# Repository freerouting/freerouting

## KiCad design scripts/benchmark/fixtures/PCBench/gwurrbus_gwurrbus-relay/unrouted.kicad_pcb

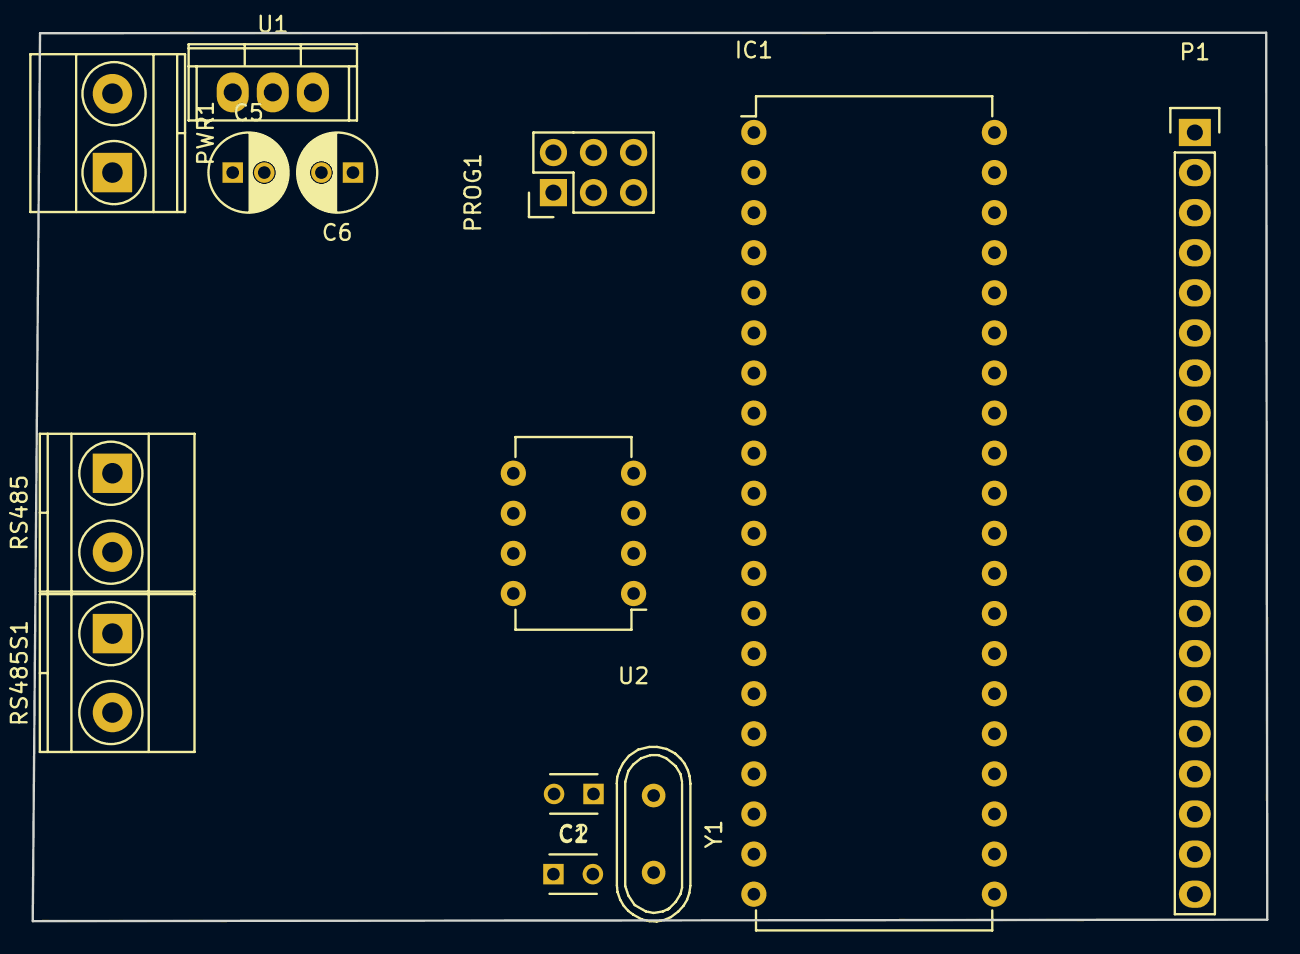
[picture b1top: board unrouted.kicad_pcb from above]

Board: 2 copper layers, 78.2 x 56.3 mm, 13 parts (0 on the bottom side), 30 nets, no tracks yet.

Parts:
C1, C2: C_Small; C_Disc_D3_P2.5
C5, C6: 10uf; C_Radial_D5_L11_P2
IC1: AT90S8515-P; DIP-40_W15.24mm
P1: CONN_01X20; Pin_Header_Straight_1x20
PROG1: CONN_02X03; Pin_Header_Straight_2x03
PWR1: CONN_01X02; TerminalBlock_Pheonix_MKDS1.5-2pol
RS485, RS485S1: CONN_01X02; TerminalBlock_Pheonix_MKDS1.5-2pol
U1: LM7805CT; TO-220
U2: SP3485CP; DIP-8_W7.62mm
Y1: 16mhz; Crystal_HC49-U_Vertical

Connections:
+5V: C6.1, IC1.40, PROG1.2, U1.3, U2.8
+BATT: C5.1, PWR1.2, U1.1
/MISO: IC1.7, PROG1.1
/MOSI: IC1.6, PROG1.4
/O1: IC1.39, P1.1
/O2: IC1.38, P1.2
/O3: IC1.37, P1.3
/O4: IC1.36, P1.4
/O5: IC1.35, P1.5
/O6: IC1.34, P1.6
/O7: IC1.33, P1.7
/O8: IC1.32, P1.8
/O9: IC1.21, P1.16
/O10: IC1.22, P1.15
/O11: IC1.23, P1.14
/O12: IC1.24, P1.13
/O13: IC1.25, P1.12
/O14: IC1.26, P1.11
/O15: IC1.27, P1.10
/O16: IC1.28, P1.9
/RESET: IC1.9, PROG1.5
/SCK: IC1.8, PROG1.3
Earth: C1.1, C2.2, C5.2, C6.2, IC1.20, P1.17, P1.18, P1.19, P1.20, PROG1.6, PWR1.1, U1.2, U2.5
unnamed: C1.2, IC1.19, Y1.2
unnamed: C2.1, IC1.18, Y1.1
unnamed: IC1.10, U2.1
unnamed: IC1.11, U2.4
unnamed: IC1.12, U2.2, U2.3
unnamed: RS485.1, RS485S1.1, U2.6
unnamed: RS485.2, RS485S1.2, U2.7

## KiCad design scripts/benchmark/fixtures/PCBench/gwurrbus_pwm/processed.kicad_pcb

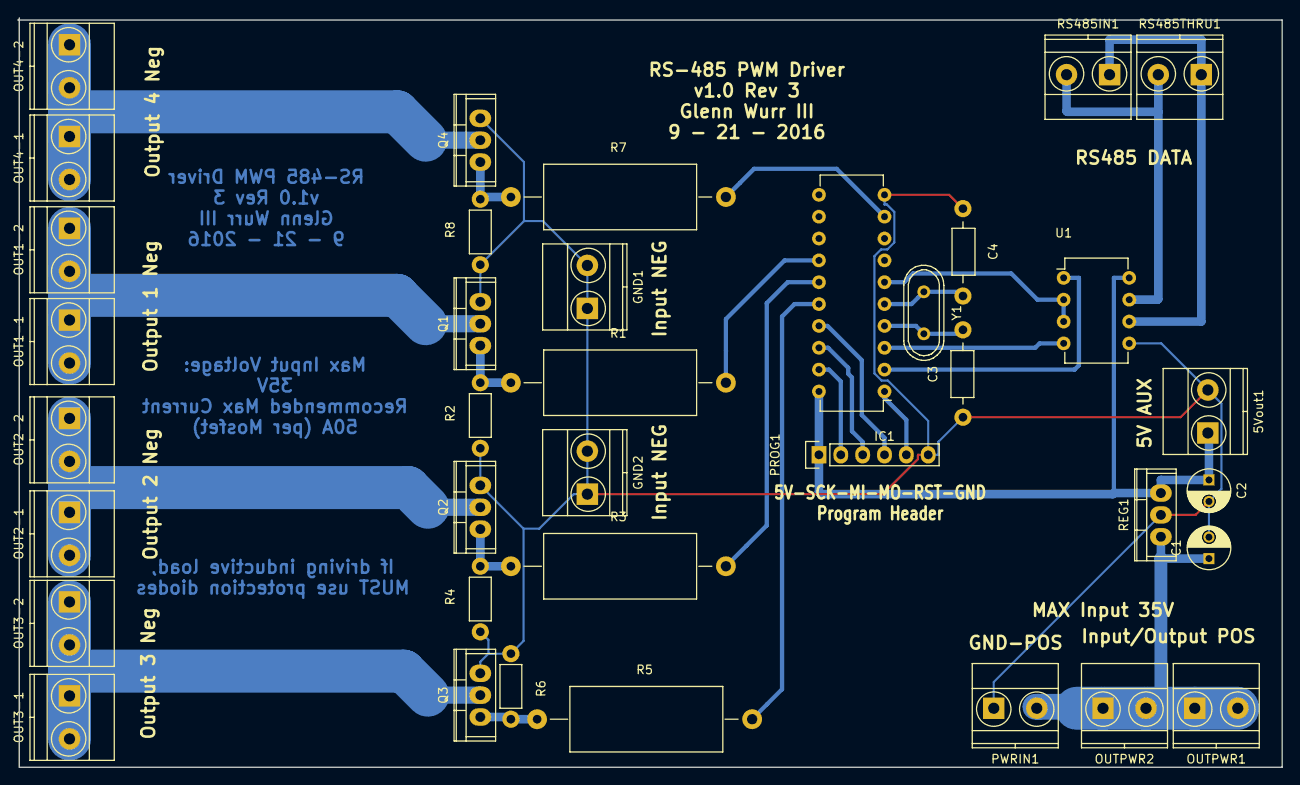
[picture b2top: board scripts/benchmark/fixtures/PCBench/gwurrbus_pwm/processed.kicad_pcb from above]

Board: 2 copper layers, 147.0 x 87.1 mm, 37 parts (0 on the bottom side), 26 nets.

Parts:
5Vout1: CONN_01X02; TerminalBlock_Pheonix_MKDS1.5-2pol
C1: 1uf; C_Radial_D5_L6_P2.5
C2: 10uf; C_Radial_D5_L6_P2.5
C3, C4: C_Small; Choke_Horizontal_RM10mm
GND1, GND2: CONN_01X02; TerminalBlock_Pheonix_MKDS1.5-2pol
IC1: ATTINY2313A-P; DIP-20_W7.62mm
OUT1-1, OUT1-2, OUT2-1, OUT2-2, OUT3-1, OUT3-2, OUT4-1, OUT4-2: CONN_01X02; TerminalBlock_Pheonix_MKDS1.5-2pol
OUTPWR1, OUTPWR2: CONN_01X02; TerminalBlock_Pheonix_MKDS1.5-2pol
PROG1: CONN_01X06; Pin_Header_Straight_1x06
PWRIN1: CONN_01X02; TerminalBlock_Pheonix_MKDS1.5-2pol
Q1, Q2, Q3, Q4: IRF540N; TO-220
R1, R3, R5, R7: 68R; Resistor_Horizontal_RM25mm
R2, R4, R6, R8: 2.2k; Resistor_Horizontal_RM7mm
REG1: LM7805CT; TO-220
RS485IN1, RS485THRU1: CONN_01X02; TerminalBlock_Pheonix_MKDS1.5-2pol
U1: SP3485CP; DIP-8_W7.62mm
Y1: Crystal; Crystal_HC49-U_Vertical

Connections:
+5V: 5Vout1.1, C2.1, IC1.20, PROG1.1, REG1.3, U1.8
/MISO: IC1.18, PROG1.3
/MOSI: IC1.17, PROG1.4
/OUT1: OUT1-1.1, OUT1-1.2, OUT1-2.1, OUT1-2.2, Q1.2
/OUT2: OUT2-1.1, OUT2-1.2, OUT2-2.1, OUT2-2.2, Q2.2
/OUT3: OUT3-1.1, OUT3-1.2, OUT3-2.1, OUT3-2.2, Q3.2
/OUT4: OUT4-1.1, OUT4-1.2, OUT4-2.1, OUT4-2.2, Q4.2
/PWM1: IC1.14, R1.2
/PWM2: IC1.15, R3.2
/PWM3: IC1.16, R5.2
/PWM4: IC1.9, R7.2
/RESET: IC1.1, PROG1.5
/RS485A: RS485IN1.1, RS485THRU1.1, U1.6
/RS485B: RS485IN1.2, RS485THRU1.2, U1.7
/SCK: IC1.19, PROG1.2
Earth: 5Vout1.2, C1.2, C2.2, C3.1, C4.1, GND1.1, GND1.2, GND2.1, GND2.2, IC1.10, PROG1.6, PWRIN1.1, Q1.3, Q2.3, Q3.3, Q4.3, R2.1, R4.1, R6.1, R8.1, REG1.2, U1.5
unnamed: C3.2, IC1.4, Y1.2
unnamed: C4.2, IC1.5, Y1.1
unnamed: IC1.2, U1.1
unnamed: IC1.3, U1.4
unnamed: IC1.6, U1.2, U1.3
unnamed: Q1.1, R1.1, R2.2
unnamed: Q2.1, R3.1, R4.2
unnamed: Q3.1, R5.1, R6.2
unnamed: Q4.1, R7.1, R8.2
VCC: C1.1, OUTPWR1.1, OUTPWR1.2, OUTPWR2.1, OUTPWR2.2, PWRIN1.2, REG1.1

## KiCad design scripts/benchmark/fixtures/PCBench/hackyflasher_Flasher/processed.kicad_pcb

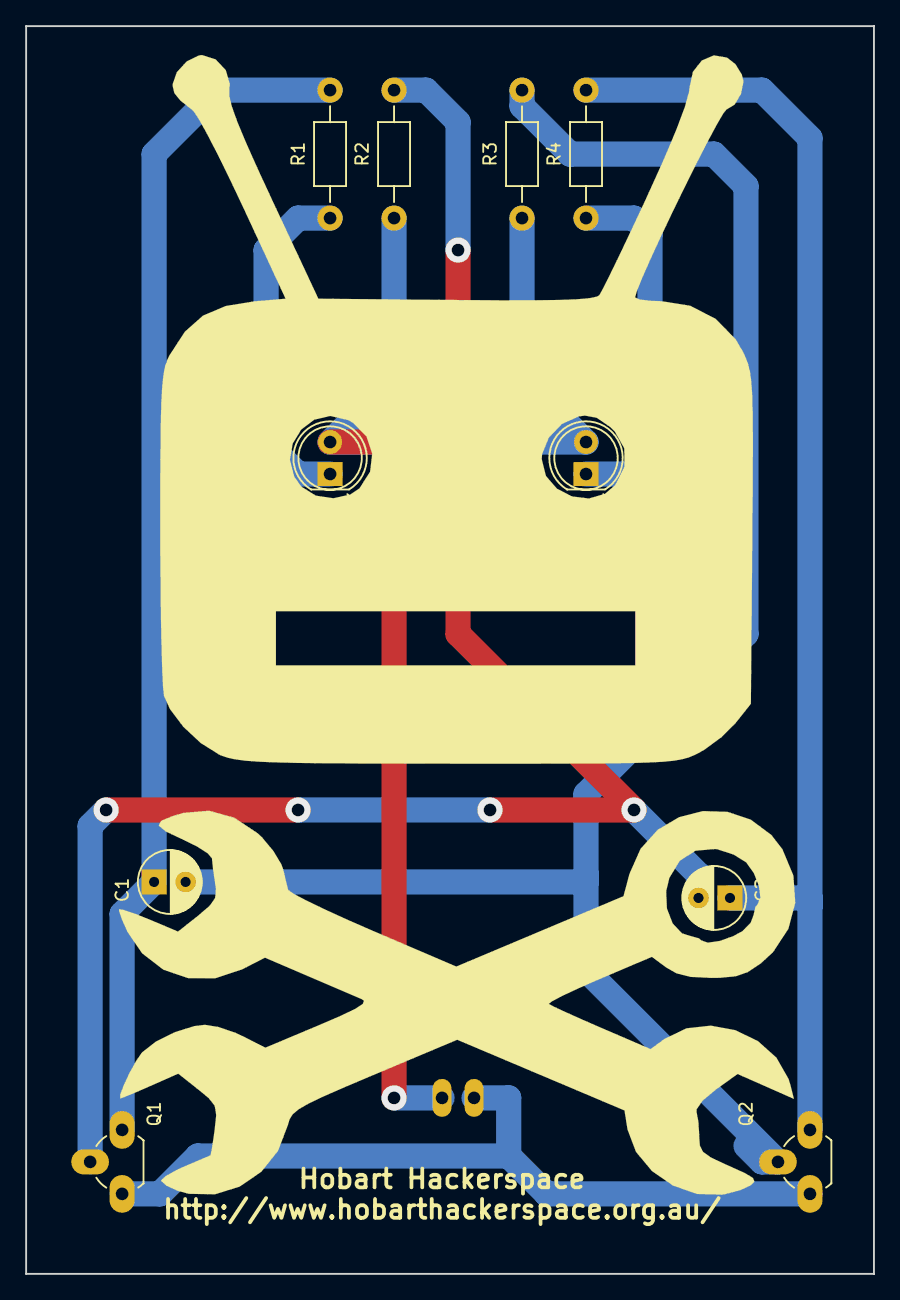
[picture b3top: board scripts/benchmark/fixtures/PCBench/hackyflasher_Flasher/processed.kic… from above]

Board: 2 copper layers, 67.3 x 99.1 mm, 11 parts (1 on the bottom side), 8 nets.

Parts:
BT1: 9V Battery; PINHEAD1-2
C1, C2: 10uF; C_Radial_D5_L6_P2.5-large-pads
D1, D2: LED; LED-5MM
Q1, Q2: 2N3904; TO-92_Rugged
R1, R4: 470; Resistor_Horizontal_RM10mm
R2, R3: 100k; Resistor_Horizontal_RM10mm

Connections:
+9V: BT1.1, D1.2, D2.2, R2.1, R3.1
GND: BT1.2, Q1.1, Q2.1
unnamed: C1.1, Q1.3, R1.2
unnamed: C1.2, Q2.2, R3.2
unnamed: C2.1, Q2.3, R4.2
unnamed: C2.2, Q1.2, R2.2
unnamed: D1.1, R1.1
unnamed: D2.1, R4.1

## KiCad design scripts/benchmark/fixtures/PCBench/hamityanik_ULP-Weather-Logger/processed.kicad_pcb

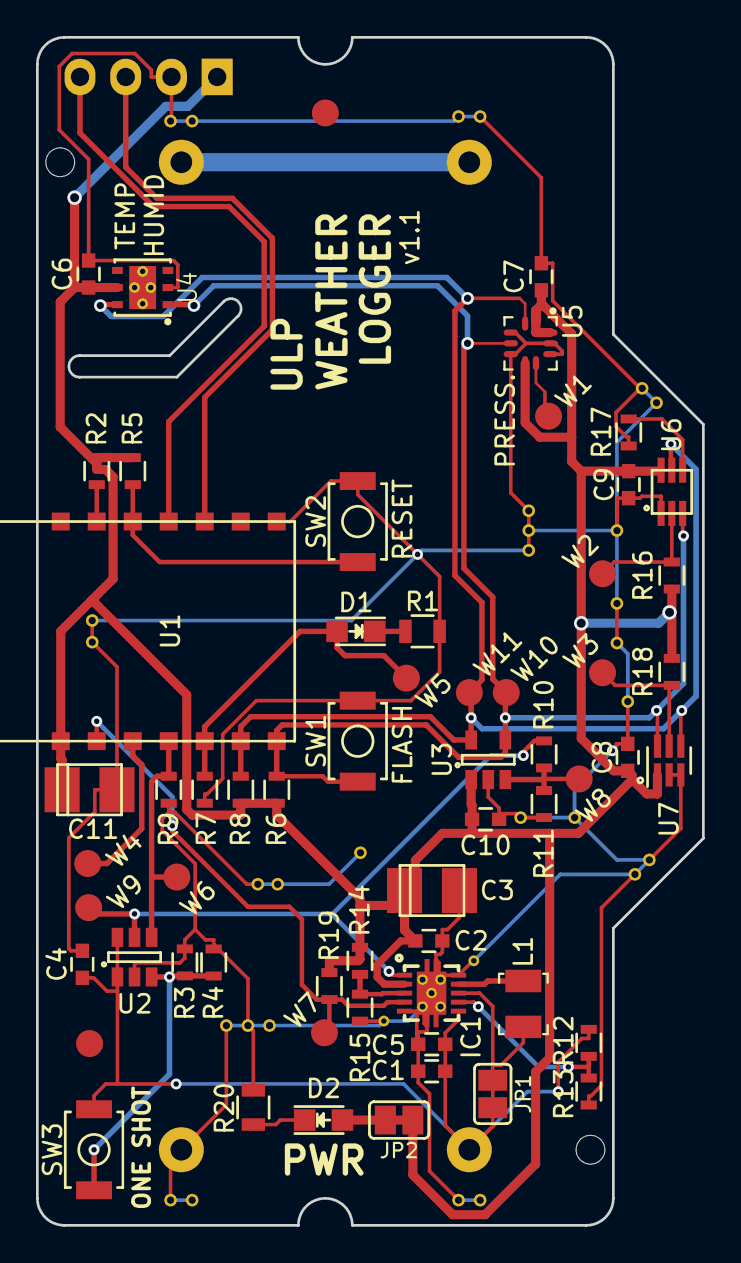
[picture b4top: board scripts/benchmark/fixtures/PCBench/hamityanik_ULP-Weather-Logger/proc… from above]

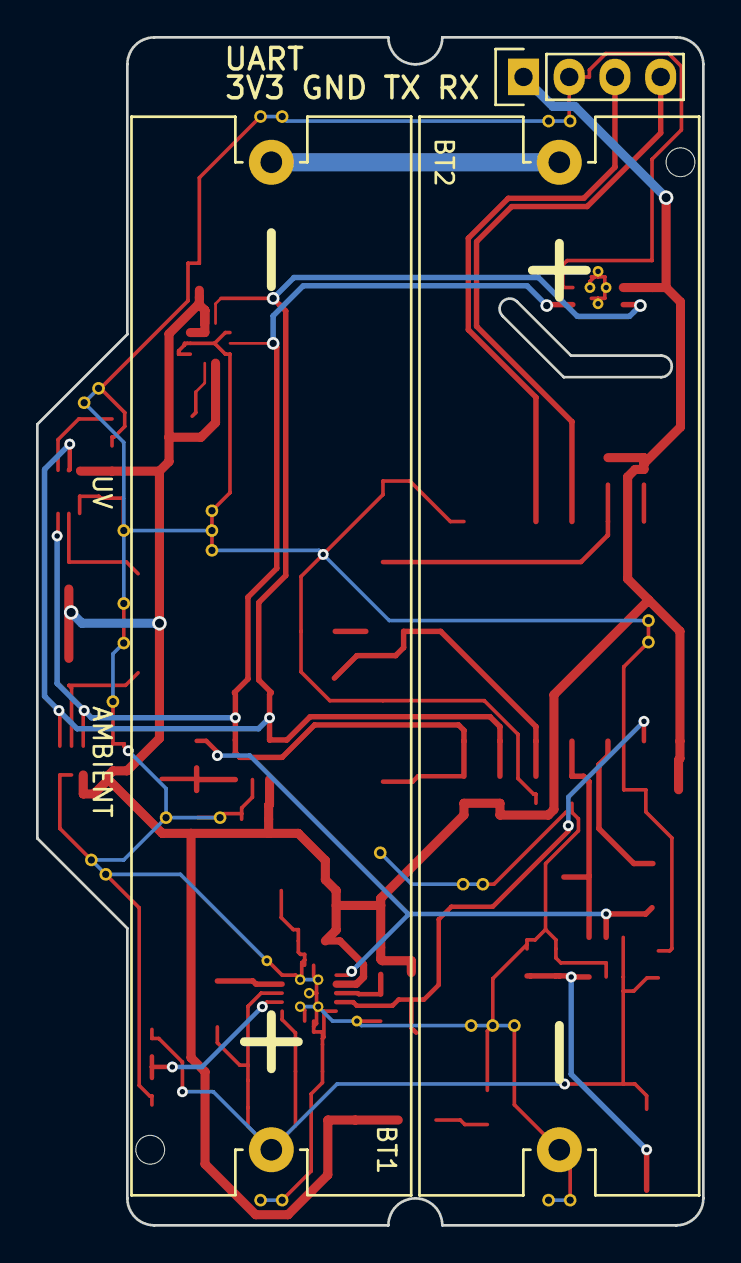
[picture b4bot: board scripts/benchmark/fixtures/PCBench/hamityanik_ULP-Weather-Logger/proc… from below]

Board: 2 copper layers, 37.0 x 66.0 mm, 63 parts (3 on the bottom side), 26 nets.

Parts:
BT1, BT2: 1015; Keystone_1015_Holder_Battery_AA
C1: 10uF; C_0603
C2: 2.2uF; C_0603
C3: 100uF; TantalC_SizeB_EIA-3528_Reflow
C4, C5, C6, C7, C8, C9, C10: 0.1uF; C_0603
C11: DNP; TantalC_SizeB_EIA-3528_Reflow
D1, D2: LTST-C170KRKT; LED_0805
FID1, FID2: FIDUCIAL; Fiducial
IC1: TPS61025; TI_DRC_S-PVSON-N10
JP1, JP2: JUMPER; SJ_OPEN
L1: 6.8uH; Inductor_1210
P1: CONN_01X04; Pin_Header_Straight_1x04
R1, R20: 1k; R_0805
R2, R13, R14: 0R; R_0603
R3: 140k; R_0603
R4: 174k; R_0603
R5, R6, R7, R8, R9, R16, R18: 10k; R_0603
R10: 1k; R_0603
R11: 390k; R_0603
R12, R15: DNP; R_0603
R17: 270k; R_0603
R19: 1M; R_0603
SW1, SW2, SW3: PTS820 J15M SMTR LFS; Tact_Switch_Top_PTS820
U1: ESP8266-ESP-03
U2: TPL5111; SOT-23-6
U3: MCP3021; SOT-23-5
U4: HDC1080; WSON-6-PAD
U5: LPS25HB; ST_LPS25HB
U6: VEML6070; OPLGA6
U7: TSL2561; WDFN-6_2x2mm_Pitch0.65mm
W1: PRES_INT; Measurement_Point_Round-SMD-Pad_Small
W2: UV_INT; Measurement_Point_Round-SMD-Pad_Small
W3: AMB_INT; Measurement_Point_Round-SMD-Pad_Small
W4: GPIO_12; Measurement_Point_Round-SMD-Pad_Small
W5: L; Measurement_Point_Round-SMD-Pad_Small
W6: DONE; Measurement_Point_Round-SMD-Pad_Small
W7: LOWBATT; Measurement_Point_Round-SMD-Pad_Small
W8: BATT_VOUT; Measurement_Point_Round-SMD-Pad_Small
W9: DRVn; Measurement_Point_Round-SMD-Pad_Small
W10: SDA; Measurement_Point_Round-SMD-Pad_Small
W11: SCL; Measurement_Point_Round-SMD-Pad_Small

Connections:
+3V3: C2.1, C3.1, C6.1, C7.1, C8.1, C9.1, C10.1, C11.1, D2.2, IC1.2, JP2.1, JP2.2, P1.1, R2.1, R5.1, R6.1, R8.1, R14.1, R16.1, R18.1, R19.1, U1.8, U3.1, U4.5, U5.1, U5.6, U5.10, U6.6, U7.1
+BATT: BT1.1, C1.1, C4.1, C5.1, IC1.6, IC1.8, JP1.1, JP1.2, L1.1, R12.1, SW3.1, U2.1, U2.6
/BATT_VOUT: R10.2, R11.1, U3.3, W8.1
/DONE: R9.1, U1.11, U2.4, W6.1
/DRVn: IC1.1, R10.1, U2.5, W9.1
/FB: IC1.3, R14.2, R15.1
/GPIO_12: U1.10, W4.1
/L: D1.2, R7.1, U1.12, W5.1
/LBI: IC1.7, R12.2, R13.1
/LOWBATT: IC1.4, R19.2, U1.9, W7.1
/M_DRV: R3.1, R4.1, SW3.2, U2.3
/RX: P1.4, U1.4
/SCL: R8.2, U1.13, U3.5, U4.6, U5.2, U6.5, U7.4, W11.1
/SDA: R6.2, SW1.1, U1.14, U3.4, U4.1, U5.4, U6.3, U7.6, W10.1
/TX: P1.3, U1.3
GND: BT2.2, C1.2, C2.2, C3.2, C4.2, C5.2, C6.2, C7.2, C8.2, C9.2, C10.2, C11.2, IC1.0, IC1.5, IC1.10, P1.2, R1.2, R3.2, R4.2, R7.2, R9.2, R11.2, R13.2, R15.2, R17.1, R20.2, SW1.2, SW2.2, U1.1, U2.2, U3.2, U4.2, U5.3, U5.5, U5.8, U5.9, U6.1, U7.2, U7.3
unnamed: BT1.2, BT2.1
unnamed: D1.1, R1.1
unnamed: D2.1, R20.1
unnamed: IC1.9, L1.2
unnamed: R2.2, U1.6
unnamed: R5.2, SW2.1, U1.5
unnamed: R16.2, U6.2, W2.1
unnamed: R17.2, U6.4
unnamed: R18.2, U7.5, W3.1
unnamed: U5.7, W1.1
